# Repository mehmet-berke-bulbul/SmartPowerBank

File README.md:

# SmartPowerBank

**A 2S4P lithium-ion power bank with USB-C PD/PPS, battery protection, and embedded control.**

<p align="center"><em>KiCad 3D render of the current PCB draft. This is a design preview, not an assembled or tested device.</em></p>

| Battery | USB-C input target | USB-C output target | PCB |
| :---: | :---: | :---: | :---: |
| 2S4P · ~80 Wh | Up to 60 W PD | Up to 45 W PD/PPS | Four layers |

## Overview

SmartPowerBank explores a compact, single-port power bank architecture. A USB-C power path handles charging and output, while a dedicated battery monitor supervises the two cell groups. An STM32 controller coordinates the user interface and system behavior. The design includes current and temperature sensing, protection FETs, and a small OLED display.

The project documents the complete hardware development process: component selection, hierarchical schematics, PCB layout, design checks, and eventually prototype testing and firmware. Power figures above are **design targets**, not measured performance.

## Current status

**PCB design in progress.** The KiCad schematics, component footprints, initial placement, and a routing draft are available in this repository. The 3D views below show the layout as it stands today. PCB design rule issues, routing details, thermal behavior, protection settings, and electrical performance still require review and validation. **Do not use the current files as manufacturing-ready hardware.**

| Area | Current state |
| --- | --- |
| System architecture and component choices | Defined for this design iteration |
| Hierarchical schematic | Captured in KiCad; ERC checked during development |
| PCB | Four-layer placement and routing draft |
| BOM and primary IC datasheets | Included for review |
| Firmware, bring-up, and measured results | Pending |

## Hardware architecture

| Function | Design choice |
| --- | --- |
| Battery pack | 2S4P Molicel INR-18650-P28A concept; 7.2 V nominal, ~11.2 Ah, ~80.6 Wh |
| USB-C PD interface | TPS25751 family USB-C/PD controller; one bidirectional port |
| Charging and power management | BQ25798 buck-boost battery charger |
| Regulated power conversion | TPS552892 buck-boost converter |
| Battery monitoring and protection | BQ76907, cell-group sensing, current shunt, NTC sensing, protection FETs |
| Control and display | STM32G0-family MCU and compact OLED interface |

The schematic and BOM are the source of truth for exact part numbers, connections, and fitted components. Battery protection thresholds and operating limits must be confirmed before any physical prototype is powered.

## PCB previews

| Top view | Bottom view |
| :---: | :---: |
|  |  |

These are design renders; the copper layout and component placement may change as routing and design-rule review continue.

## Explore the repository

| Path | Contents |
| --- | --- |
| [`hardware/kicad/`](hardware/kicad/) | KiCad project, schematic sheets, PCB, and project libraries |
| [`hardware/bom/`](hardware/bom/) | Component lists and sourcing work |
| [`hardware/datasheets/`](hardware/datasheets/) | Datasheets for the principal ICs |
| [`hardware/mechanical/`](hardware/mechanical/) | Mechanical design work |
| [`assets/images/`](assets/images/) | PCB previews and project images |
| [`docs/`](docs/) | Requirements and engineering notes |
| [`firmware/`](firmware/) | Firmware workspace; implementation pending |
| [`manufacturing/`](manufacturing/) | Reserved for reviewed production outputs |

Open the project with **KiCad 9** from `hardware/kicad/SmartPowerBank/`. Inspect the schematic, PCB, BOM, and design-rule results together; the renders alone do not establish electrical correctness.

## Next milestones

1. Resolve PCB DRC violations and remaining routing issues.
2. Review current paths, switching loops, ground references, creepage/clearances, and thermal copper against component guidance.
3. Reconcile the BOM with exact manufacturer part numbers, footprints, and availability.
4. Finalize the mechanical design and firmware bring-up plan.
5. Build and test a prototype only after the electrical and safety reviews are complete.

---

**Project by Mehmet Berke Bülbül** · Electrical and Electronics Engineering · Bursa Technical University

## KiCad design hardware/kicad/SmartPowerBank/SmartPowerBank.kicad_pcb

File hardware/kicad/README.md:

# KiCad Workspace

Create the KiCad project here with this exact name:

`SmartPowerBank`

Create these hierarchical schematic sheets:

1. `01_USB_C_PD`
2. `02_BIDIRECTIONAL_CHARGER`
3. `03_BMS_PROTECTION`
4. `04_BATTERY_INTERFACE`
5. `05_STM32_CONTROL`
6. `06_DISPLAY_UI`
7. `07_TEMPERATURE_SENSING`
8. `08_DEBUG_PROGRAMMING`
9. `09_TESTPOINTS_AND_SERVICE`

Do not begin PCB placement until the schematic has passed ERC and the component decision log is updated.

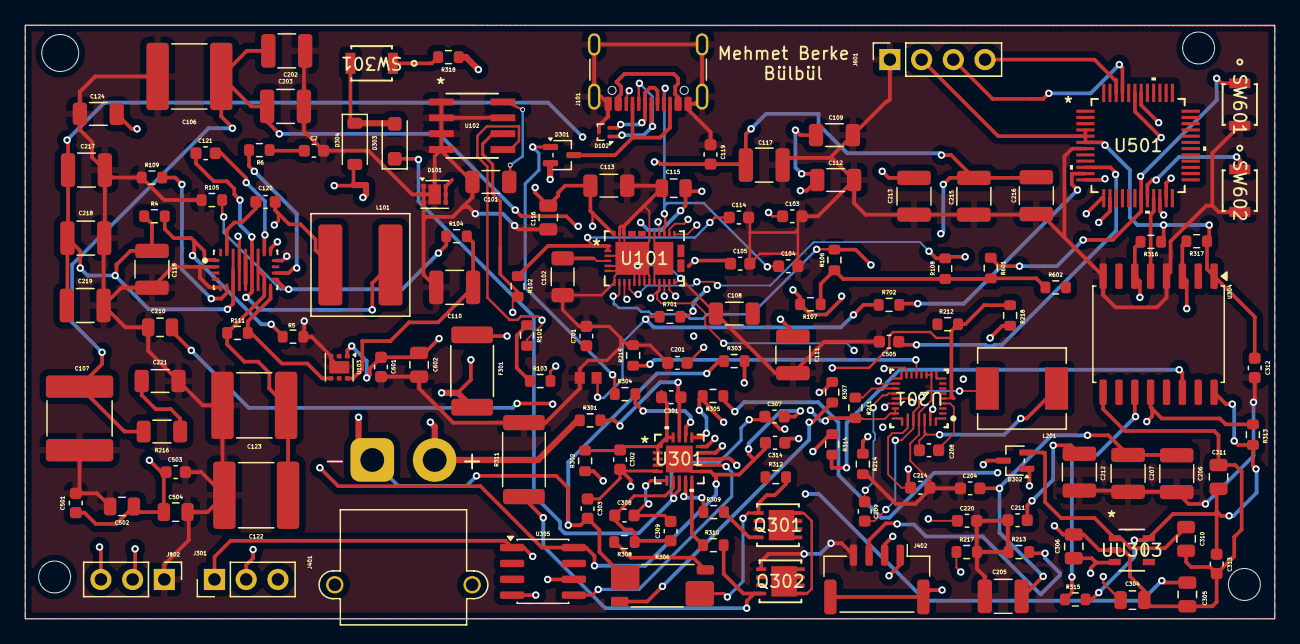
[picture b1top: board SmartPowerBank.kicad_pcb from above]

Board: 4 copper layers, 100.1 x 47.5 mm, 143 parts (0 on the bottom side), 86 nets.

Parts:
C2: 22 nF; C_0603_1608Metric
C101: 10 µF X7R / 10v; C_1206_3216Metric
C102: 10 µF X7R / >6.3v; C_1206_3216Metric
C103, C104: 330 pF, 50 V, C0G; C_0603_1608Metric
C105: 100 nF,50 V,X7R; C_0603_1608Metric
C106, C107: 22 µ,35 V,X7R; C_2220_5750Metric
C108: 4.7uF, X7R,35V; C_1206_3216Metric
C109, C112: 10 µF,10 V; C_1206_3216Metric
C110: 100 µF,10 V; C_1210_3225Metric
C111: 100µF,10 V; C_1210_3225Metric
C113: 10uF,10V,X7R; C_1206_3216Metric
C114: 100nF,10V,X7R; C_0603_1608Metric
C115, C116: 1 µF, 10 V, X7R; C_0805_2012Metric
C117, C118: 20 µF, 25 V, X7R; C_1210_3225Metric
C119: 100 nF, 50 V, X7R; C_0603_1608Metric
C120, C121: 100 nF, 25 V, X7R; C_0603_1608Metric
C122, C123: 47 µF, 25 V, X7R; C_2220_5750Metric
C124: 10 µF / ≥10 V; C_1206_3216Metric
C201, C204: 100nF, 50V; C_0603_1608Metric
C202, C203, C205, C206, C207: 10uF, 35V, X7R; C_1210_3225Metric
C208, C209: 47nF, 25V, X7R; C_0603_1608Metric
C210: 4.7uF, 10V, X7R; C_0805_2012Metric
C211, C214: 100nF, 25V, X7R; C_0603_1608Metric
C212, C213, C215, C216, C217, C218, C219: 10uF, 25V, X7R; C_1210_3225Metric
C220: 1nF, 50V, C0G/NP0; C_0603_1608Metric
C221: 2.2 µF,50 V, X7R; C_1206_3216Metric
C301, C302, C303: 220nF; C_0603_1608Metric
C304, C305, C306: 1uF; C_0805_2012Metric
C307: 470pF; C_0603_1608Metric
C308: 100nF; C_0603_1608Metric
C309: 100pF / DNP; C_0603_1608Metric
C310: 1 µF / 25 V,X7R; C_0805_2012Metric
C311: 1 µF / 10 V,X7R; C_0805_2012Metric
C312, C313: 100 nF / 25 V,X7R; C_0603_1608Metric
C314: 100 nF; C_0603_1608Metric
C501, C503, C505, C601: 100 nF,≥10 V,X7R; C_0603_1608Metric
C502, C602: 4,7 µF,≥10 V,X7R; C_0805_2012Metric
C504: 1 µF,≥10 V,X7R; C_0805_2012Metric
C701: 100 nF, ≥10 V, X7R; C_0603_1608Metric
D101: TVS2200DRVR; WSON-6-1EP_2x2mm_P0.65mm_EP1x1.6mm
D102: TPD2EUSB30DRTR; Texas_DRT-3
D301, D302: BAS40W-7-F; SOT-323_SC-70
D303: schottky; D_SOD-123F
D304: 1,8 V zener; D_SOD-123
F301: 15A; Fuse_2512_6332Metric
J101: USB_C_PD_RECEPTACLE; USB_C_Receptacle_GCT_USB4105-xx-A_16P_TopMnt_Horizontal
J301, J802: Conn_01x03; PinHeader_1x03_P2.54mm_Vertical
J401: XT30PW-M; AMASS_XT30PW-M_1x02_P2.50mm_Horizontal
J402: BM04B-GHS-TBT; JST_GH_BM04B-GHS-TBT_1x04-1MP_P1.25mm_Vertical
J601: ER-OLEDM0.96-1W-I2C; PinSocket_1x04_P2.54mm_Vertical
L101: 4.7 µH; L_Coilcraft_XAL7070-XXX
L201: 1uH; IND_SPM6530T-1R0M120
NT301: BATT_N_TO_BMS_VSS; NetTie-2_SMD_Pad0.5mm
Q301, Q302: AON7296; DFN3X3A_8L_EPA1_P_AOS
Q701: NCU18XH103F60RB; TRES_NCU18XH103F6SRB_MUR
R4, R104: 100 kΩ; R_0603_1608Metric
R5: 37,6 kΩ; R_0603_1608Metric
R6: 2,2 kΩ; R_0603_1608Metric
R101, R102, R103, R106, R107: 2.2 kΩ; R_0603_1608Metric
R105: 31,5 kΩ; R_0603_1608Metric
R108, R601, R602: 10 kΩ; R_0603_1608Metric
R109: 49,9 kΩ; R_0603_1608Metric
R111: 10 mΩ, ≥1 W; R_0603_1608Metric
R211, R304, R307, R308: 100R; R_0603_1608Metric
R212: 5.23kR; R_0603_1608Metric
R213: 30.1kR; R_0603_1608Metric
R214: 6.04k, 1%; R_0603_1608Metric
R215: 10kR; R_0603_1608Metric
R216: 2ohm; R_1206_3216Metric
R217: 100kR; R_0603_1608Metric
R218: 47.5kR; R_0603_1608Metric
R301, R302, R303, R305: 10R; R_0603_1608Metric
R306: 2 mΩ_2W_50ppm; R_Shunt_Vishay_WSK2512_6332Metric_T1.19mm
R309, R310: 5.1kR; R_0603_1608Metric
R311: 10MR; R_2512_6332Metric
R312: 10MR; R_0603_1608Metric
R313, R314, R315, R316, R317: 4.7kR; R_0603_1608Metric
R318, R702: 1 kΩ; R_0603_1608Metric
R701: 39 kΩ; R_0603_1608Metric
SW301, SW601, SW602: B3U-1000P
U101: TPS25751DREFR; WQFN38_REF_TEX
U102: 24FC512-I/SN; SOIC8_4P9X3P9MC_MCH
U103: TLV75533PDRV; WSON-6-1EP_2x2mm_P0.65mm_EP1x1.6mm
U104: TPS552892RYQR; RYQ0021A-MFG
U201: BQ25798RQMR; RQM0029A-MFG
U301: BQ76907RGR; VQFN20_RGR_TEX
U304: ISO1642DWR; SOIC-16W_7.5x10.3mm_P1.27mm
U305: ATtiny402-SS; SOIC-8_3.9x4.9mm_P1.27mm
U501: STM32G0B1CBT6; LQFP48_STM32G0B1CBT_STM
UU303: TPS7A2433DBVR; SOT23_DBV_TEX

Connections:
/01_USB_C_PD/I2CC_IRQ: R103.2, U101.18 (*I2CC_IRQ), U201.21 (INT_N)
/01_USB_C_PD/I2CC_SCL: R102.2, U101.17 (I2CC_SCL), U102.6 (SCL), U201.14 (SCL)
/01_USB_C_PD/I2CC_SDA: R101.2, U101.16 (I2CC_SDA), U102.5 (SDA), U201.15 (SDA)
/01_USB_C_PD/I2C_PD_SCL: R107.2, U101.9 (I2CT_SCL), U501.22 (PB10)
/01_USB_C_PD/I2C_PD_SDA: R106.2, U101.8 (I2CT_SDA), U501.23 (PB11)
/01_USB_C_PD/PD_5V: C109.1, C110.1, C111.1, C112.1, C115.1, R104.2, R111.2, U101.34 (PP5V), U101.35 (PP5V), U103.4 (EN), U103.6 (IN), U104.13 (ISN)
/01_USB_C_PD/PD_ALERT: R108.2, U101.10 (*I2CT_IRQ), U501.12 (PA1)
/01_USB_C_PD/PD_DRAIN: U101.15 (DRAIN), U101.30 (DRAIN), U101.40 (DRAIN)
/01_USB_C_PD/PD_LDO1V5: C102.1, U101.4 (LDO_1V5)
/01_USB_C_PD/PD_LDO3V3: C101.1, C114.2, R101.1, R102.1, R103.1, U101.1 (LDO_3V3), U101.2 (ADCIN1), U102.8 (VCC)
/01_USB_C_PD/USB_CC1: C104.1, J101.A5 (CC1), U101.28 (CC1)
/01_USB_C_PD/USB_CC2: C103.1, J101.B5 (CC2), U101.29 (CC2)
/01_USB_C_PD/USB_DM: D102.2 (D-), J101.A7 (D-), J101.B7 (D-), U101.27 (GPIO5/USB_N/LD2)
/01_USB_C_PD/USB_DP: D102.1 (D+), J101.A6 (D+), J101.B6 (D+), U101.26 (GPIO4/USB_P/LD1)
/01_USB_C_PD/USB_VBUS: C108.2, D101.4 (IN), D101.5 (IN), D101.6 (IN), J101.A4 (VBUS), J101.A9 (VBUS), J101.B4 (VBUS), J101.B9 (VBUS), U101.23 (VBUS_IN), U101.24 (VBUS_IN), U101.25 (VBUS_IN), U101.32 (VBUS), U101.33 (VBUS)
/01_USB_C_PD/VBUS: C105.1, C106.1, C107.1, C201.1, C202.2, C203.1, R216.2, U101.20 (PPHV), U101.21 (PPHV), U101.22 (PPHV), U201.2 (VBUS), U201.3 (VBUS), U201.8 (VAC2), U201.9 (VAC1)
/02_BIDIRECTIONAL_CHARGER/PACK_P: C211.1, C212.2, C213.1, F301.1, R211.2, U201.22 (BAT), U201.23 (BAT)
/02_BIDIRECTIONAL_CHARGER/PMID: C204.1, C205.2, C206.1, C207.1, U201.29 (PMID)
/02_BIDIRECTIONAL_CHARGER/REGN: C210.2, R212.2, R218.2, U201.5 (REGN)
/02_BIDIRECTIONAL_CHARGER/TS: J402.3, R212.1, R213.2, U201.16 (TS)
/03_BMS_PROTECTION/BATT_N: C303.2, J401.1, NT301.1, R303.1, R306.1
/03_BMS_PROTECTION/BATT_P: C310.1, D301.2 (A), D302.2 (A), F301.2, J401.2, R301.1, R318.1, UU303.1 (IN)
/03_BMS_PROTECTION/BMS_3V3: C311.1, C313.1, C314.1, J301.1, R313.1, R314.1, R315.1, U304.16 (VCC2), U305.1 (VCC), UU303.5 (OUT)
/03_BMS_PROTECTION/BMS_ALERT: U304.5 (OUTB), U501.21 (PB2)
/03_BMS_PROTECTION/BMS_VSS: C304.2, C305.2, C306.2, C307.2, C310.2, C311.2, C313.2, C314.2, D304.2 (A), J301.2, NT301.2, U301.11 (VSS), U301.21 (EPAD), U304.9 (GND2), U305.8 (GND), UU303.2 (GND)
/03_BMS_PROTECTION/BQ_ALERT: R313.2, U301.14 (ALERT), U304.12 (INB)
/03_BMS_PROTECTION/BQ_BAT: C304.1, R304.2, U301.17 (BAT)
/03_BMS_PROTECTION/BQ_REGOUT: C306.1, U301.15 (REGOUT), UU303.3 (EN)
/03_BMS_PROTECTION/BQ_REGSRC: C305.1, R305.2, U301.16 (REGSRC)
/03_BMS_PROTECTION/BQ_SCL: R315.2, U301.12 (SCL), U304.11 (SCL2), U305.5 (PA2)
/03_BMS_PROTECTION/BQ_SDA: R314.2, U301.13 (SDA), U304.14 (SDA2), U305.4 (PA1)
/03_BMS_PROTECTION/CELL1: J402.1, R302.1
/03_BMS_PROTECTION/CHG_GATE: R310.1, U301.10 (CHG)
/03_BMS_PROTECTION/DSG_GATE: R309.1, U301.9 (DSG)
/03_BMS_PROTECTION/FET_MID: Q301.8, Q302.5
/03_BMS_PROTECTION/FET_SIDE_N: Q301.1, R306.4, R312.2
/03_BMS_PROTECTION/I2C_BMS_SCL: R316.2, U304.6 (SCL1), U501.42 (PB3)
/03_BMS_PROTECTION/I2C_BMS_SDA: R317.2, U304.3 (SDA1), U501.43 (PB4)
/03_BMS_PROTECTION/NTC_BAT: C307.1, D303.1 (K), J402.2, U301.8 (TS)
/03_BMS_PROTECTION/SRN_FILT: C308.1, C309.1, R308.1, U301.7 (SRN)
/03_BMS_PROTECTION/SRP_FILT: C308.2, C309.2, R307.1, U301.6 (SRP)
/03_BMS_PROTECTION/UPDI: J301.3, U305.6 (~RESET/PA0)
/03_BMS_PROTECTION/VC0_FILT: C302.2, C303.1, R303.2, U301.5 (VC0)
/03_BMS_PROTECTION/VC7_FILT: C301.1, R301.2, U301.18 (VC7)
/03_BMS_PROTECTION/VC_MID_FILT: C301.2, C302.1, R302.2, U301.1 (VC4), U301.2 (VC3), U301.3 (VC2), U301.4 (VC1), U301.19 (VC6), U301.20 (VC5)
/03_BMS_PROTECTION/WAKE: D303.2 (A), D304.1 (K), SW301.2
/05_STM32_CONTROL/BTN_MODE: R602.2, SW602.1, U501.20 (PB1)
/05_STM32_CONTROL/BTN_PWR: R601.1, SW601.1, U501.19 (PB0)
/05_STM32_CONTROL/I2C_UI_SCL: J601.3, U501.45 (PB6)
/05_STM32_CONTROL/I2C_UI_SDA: J601.4, U501.46 (PB7)
/05_STM32_CONTROL/NRST: C505.1, U501.10 (PF2-NRST)
/05_STM32_CONTROL/NTC_PWR_ADC: C701.1, R702.2, U501.11 (PA0)
/05_STM32_CONTROL/UART_DBG_RX: J802.3, U501.14 (PA3)
/05_STM32_CONTROL/UART_DBG_TX: J802.2, U501.13 (PA2)
unnamed: C2.2, R6.1
unnamed: C221.1, R216.1
unnamed: D301.1 (K), R304.1
unnamed: D302.1 (K), R305.1
unnamed: Q301.4, R309.2, R312.1
unnamed: Q302.4, R310.2, R311.1
unnamed: Q701.2, R701.2, R702.1
unnamed: R306.2, R307.2
unnamed: R306.3, R308.2
unnamed: R318.2, SW301.1
unnamed: C120.1, U104.20 (BOOT1)
unnamed: C121.2, U104.19 (BOOT2)
unnamed: R6.2, U104.15 (COMP)
unnamed: R4.2, R5.1, U104.1 (EN_UVLO)
unnamed: R104.1, R105.1, U104.14 (FB)
unnamed: R109.2, U104.6 (FSW)
unnamed: C122.1, C123.1, R111.1, U104.11 (VOUT), U104.12 (ISP)
unnamed: C120.2, L101.1, U104.8 (SW1)
unnamed: C121.1, L101.2, U104.10 (SW2)
unnamed: C124.1, U104.18 (VCC)
unnamed: R211.1, U201.18 (BATP)
unnamed: C208.1, U201.4 (BTST1)
unnamed: C209.1, U201.19 (BTST2)
unnamed: R215.1, U201.13 (CE_N)
unnamed: R217.1, R218.1, U201.17 (ILIM_HIZ)
unnamed: R214.1, U201.20 (PROG)
unnamed: C220.1, U201.24 (SDRV)
unnamed: C208.2, L201.1, U201.28 (SW1)
unnamed: C209.2, L201.2, U201.26 (SW2)
PACK_N: C2.1, C101.2, C102.2, C103.2, C104.2, C105.2, C106.2, C107.2, C108.1, C109.2, C110.2, C111.2, C112.2, C113.2, C114.1, C115.2, C116.2, C117.2, C118.2, C119.2, C122.2, C123.2, C124.2, C201.2, C202.1, C203.2, C204.2, C205.1, C206.2, C207.2, C210.1, C211.2, C212.1, C213.2, C214.2, C215.1, C216.2, C217.1, C218.2, C219.2, C220.2, C221.2, C312.2, C501.2, C502.2, C503.1, C504.1, C505.2, C601.2, C602.2, C701.2, D101.1 (GND), D101.2 (GND), D101.3 (GND), D101.7 (GND), D102.3 (GND), J101.A1 (GND), J101.A12 (GND), J101.B1 (GND), J101.B12 (GND), J101.S1 (SHIELD), J402.4, J601.1, J802.1, Q302.1, Q701.1, R5.2, R105.2, R109.1, R213.1, R214.2, R215.2, R217.2, R311.2, SW601.2, SW602.2, U101.3 (ADCIN2), U101.5 (GPIO0), U101.6 (GPIO1), U101.7 (GPIO2), U101.11 (GND), U101.12 (GND), U101.13 (GPIO11), U101.14 (GND), U101.19 (GPIO3), U101.31 (GND), U101.36 (GPIO7), U101.37 (GPIO6), U101.39 (GND), U102.1 (A0), U102.2 (A1), U102.3 (A2), U102.4 (GND), U102.7 (WP), U103.3 (GND), U103.7 (GND), U104.2 (MODE), U104.5 (DITH_SYNC), U104.9 (PGND), U104.17 (AGND), U201.10 (ACDRV2), U201.11 (ACDRV1), U201.27 (GND), U304.4 (INA), U304.8 (GND1), U501.7 (VSS/VSSA)
PD_3V3: C113.1, C116.1, C312.1, C501.1, C502.1, C503.2, C504.2, C601.1, C602.1, J601.2, R106.1, R107.1, R108.1, R316.1, R317.1, R601.2, R602.1, R701.1, U101.38 (VIN_3V3), U103.1 (OUT), U304.1 (VCC1), U501.4 (VBAT), U501.5 (VREF+), U501.6 (VDD/VDDA)
SYS_RAW: C117.1, C118.1, C119.1, C214.1, C215.2, C216.1, C217.2, C218.1, C219.1, R4.1, U104.7 (VIN), U201.25 (SYS)
